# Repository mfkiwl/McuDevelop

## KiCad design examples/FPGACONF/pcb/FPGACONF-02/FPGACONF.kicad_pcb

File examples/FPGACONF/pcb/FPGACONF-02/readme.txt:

### 201911030:
1. FPGACONF-01 + rework
2. the board was not made

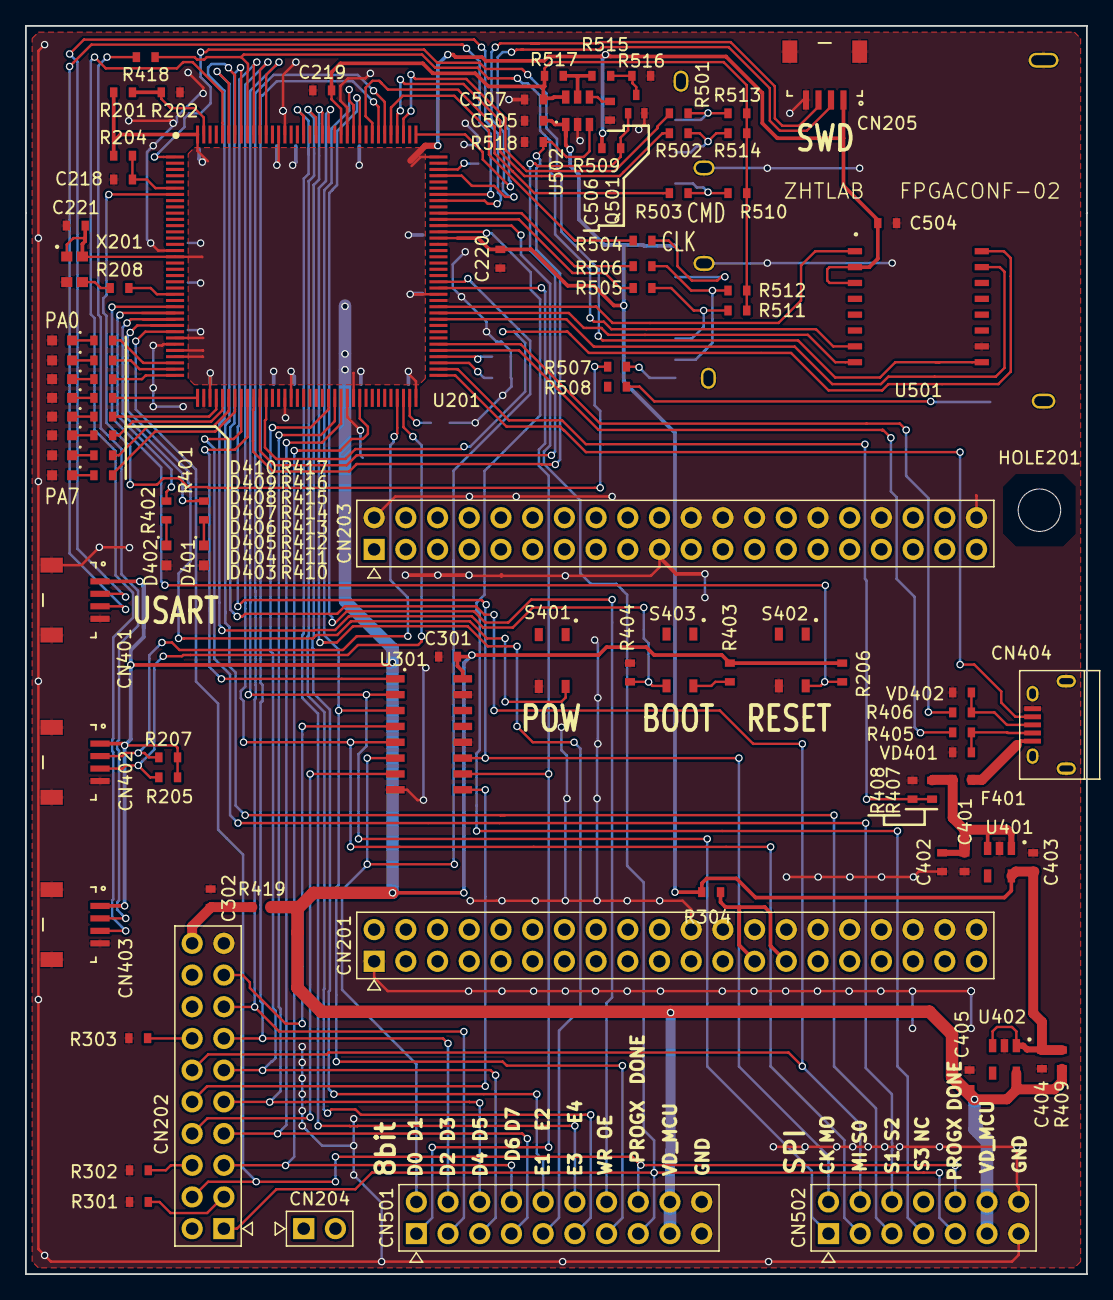
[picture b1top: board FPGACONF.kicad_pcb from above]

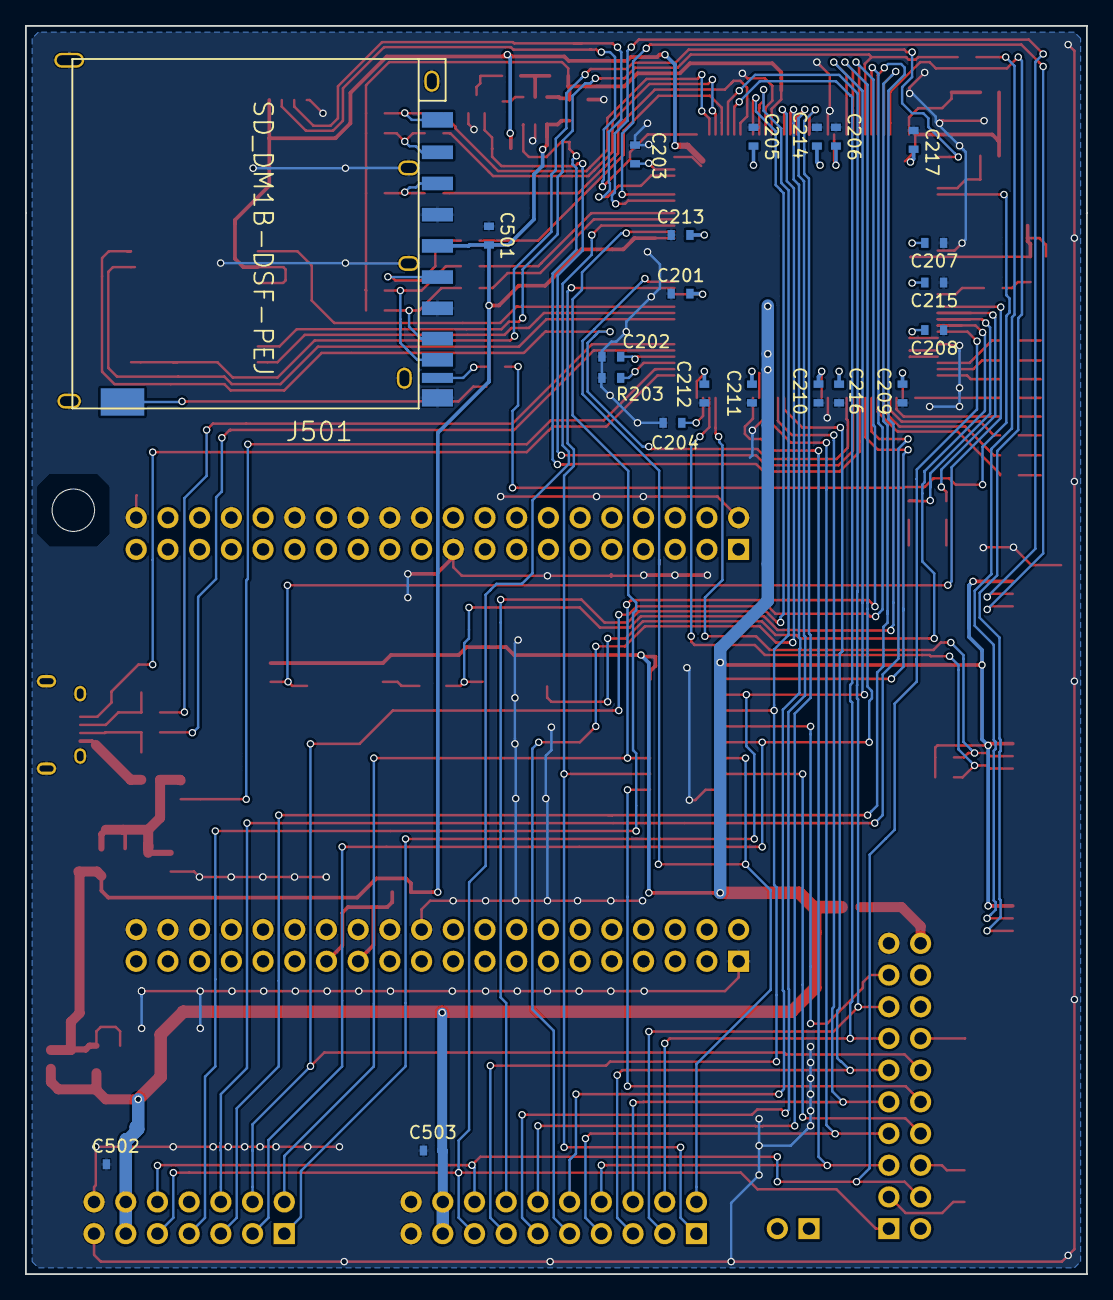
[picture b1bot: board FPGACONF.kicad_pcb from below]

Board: 2 copper layers, 85.0 x 100.0 mm, 121 parts (22 on the bottom side), 110 nets.

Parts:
C201, C205, C206, C207, C208, C209, C210, C211, C212, C217, C218, C219, C220, C221, C301, C504: 0.1u; RCL_1608m
C202, C203, C204, C302, C501, C502, C503, C507: 2.2u; RCL_1608m
C213, C214, C215, C216, C401: 10u; RCL_1608m
C402, C403, C404, C405, C505: 1u; RCL_1608m
C506: 0.01u; RCL_1608m
CN201, CN203: CN_20x2_D1.0mm_P2.54mm_TH
CN202, CN501: CN_10x2_D1.0mm_P2.54mm_TH
CN204: CN_02x1_D1.0mm_P2.54mm_TH; CN_01x2_D1.0mm_P2.54mm_TH
CN205, CN401, CN402, CN403: JST_SM04B-SRSS-TB; JST_SH_SM04B-SRSS-TB_04x1.00mm_Angled
CN404: ZX62D-B-5PA8(30); USB-uB_ZX62D-B-5PA8-30
CN502: CN_07x2_D1.0mm_P2.54mm_TH
D401, D403, D404, D405, D406, D407, D408, D409, D410: SML-E12V8TT86; LED_1608M_Rohm
D402: SML-E13BC8TT86; LED_1608M_Rohm
F401: MFU0603FF03150P500; RCL_1608m
HOLE201: HOLE_01x1_D3.4mm_P0.00mm_NTH; Hole_01x1_D3.4mm_P0.00mm_NTH
J501: SD_DM1B-DSF-PEJ
Q501: RU1C001UN; SC-85_2.0x2.0mm
R201, R205, R206, R207, R401, R402, R403, R410, R411, R412, R413, R414, R415, R416, R417, R510, R511, R512, R513, R514: 4.7k; RCL_1608m
R202, R404, R407, R509, R518: 100k; RCL_1608m
R203: 3.0k; RCL_1608m
R204, R208, R301, R302, R303, R304, R409, R419: 0; RCL_1608m
R405, R406, R418, R501, R502, R503, R504, R505, R506, R507, R508: 22; RCL_1608m
R408: 150k; RCL_1608m
R515: 7.5k; RCL_1608m
R516: 20k; RCL_1608m
R517: 13k; RCL_1608m
S401, S402, S403: SKRPABE010; Alps_SKRPABE010
U201: STM32F730Z8T; TQFP-144_20x20mm_Pitch0.5mm
U301: SN74CBTLV3257D; SOIC-16_3.9x10.0mm_Pitch1.27mm
U401: LP5907MFX-3.3/NOPB; SOT-23-5_2.7x2.9mm_Pitch0.95mm
U402: LP5907MFX-1.8/NOPB; SOT-23-5_2.7x2.9mm_Pitch0.95mm
U501: MT25QL01GBBB8ESF-0SIT; SOIC-16_10.3x10.3mm_Pitch1.27mm
U502: TPS73001DBVR; SOT-23-6_2.7x2.9mm_Pitch0.95mm
VD401, VD402: AVRL161A3R3FTA; RCL_1608m
X201: ASVTX-12-A-40.000MHZ-H10-T; SMD004_abracon_2.5x2.0mm

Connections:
FPGA_CCLK_SCK: CN202.17, U301.4
FPGA_D0_MOSI: CN202.10, U301.9
FPGA_D1_MISO: CN202.8, U301.7
MCU_BOOT: R404.2, S403.4, U201.138
MCU_PA0:LED0: R417.2, U201.34
MCU_PA1:LED1: R416.2, U201.35
MCU_PA2:LED2: R415.2, U201.36
MCU_PA3:LED3: R414.2, U201.37
MCU_PA4:LED4: R413.2, U201.40
MCU_PA5:LED5: R412.2, U201.41
MCU_PA6:LED6: R411.2, U201.42
MCU_PA7:LED7: R410.2, U201.43
MCU_PA9:UART_TXD: CN401.2, U201.101
MCU_PA10:UART_RXD: CN401.3, U201.102
MCU_PA13:SWDIO: CN205.3, U201.105
MCU_PA14:SWCLK: CN205.2, U201.109
MCU_PB0:SDMMC1_PWREN: R518.2, U201.46, U502.3
MCU_PB1:SDMMC1_VSEL33: Q501.1, R509.1, U201.47
MCU_PB2:QSPI_CLK: U201.48, U501.16
MCU_PB3:SPI1_SCK: CN502.1, U201.133, U301.2
MCU_PB4:SPI1_MISO: CN502.3, U201.134, U301.5
MCU_PB5:SPI1_MOSI: CN502.2, U201.135, U301.11
MCU_PB6:I2CS_SCL_QSPI_CSX: R418.2, U201.136, U501.7
MCU_PB7:SPI1_CS0X: CN202.12, CN502.4, U201.137
MCU_PB8:SPI1_CS1X: CN502.5, U201.139
MCU_PB9:I2CS_SDA: CN403.3, U201.140
MCU_PB10:I2CM_SCL: CN402.2, R207.1, U201.69
MCU_PB11:I2CM_SDA: CN402.3, R205.1, U201.70
MCU_PB12:USB_ID: CN404.4, U201.73
MCU_PB13:USB_VBUS_EN: R407.2, R408.2, U201.74
MCU_PB14:USB_DN: R405.2, U201.77
MCU_PB15:USB_DP: R406.2, U201.78
MCU_PC0:LED_BLUE: R402.2, U201.26
MCU_PC1:LED_RED: R401.2, U201.27
MCU_PC2:POWER_SW_X: S401.2, U201.28
MCU_PC3:FPGA_DONE: CN202.4, CN501.16, CN502.10, U201.29
MCU_PC4:SPI1_CS2X: CN502.6, U201.44
MCU_PC5:CONF_SEL: U201.45, U301.1
MCU_PC6:SPI1_CS3X: CN502.7, U201.96
MCU_PC7:FPGA_PROGX: CN202.1, CN501.15, CN502.9, U201.97
MCU_PC8:SDMMC1_D0: R505.1, U201.98
MCU_PC9:SDMMC1_D1: R506.1, U201.99
MCU_PC10:SDMMC1_D2: R501.1, U201.111
MCU_PC11:SDMMC1_D3: R502.1, U201.112
MCU_PC12:SDMMC1_CLK: R504.1, U201.113
MCU_PC13:SDMMC1_CDET_X: R507.1, U201.7
MCU_PD0:FMC_D2: CN202.15, CN501.3, U201.114
MCU_PD1:FMC_D3: CN202.13, CN501.4, U201.115
MCU_PD2:SDMMC1_CMD: R503.1, U201.116
MCU_PD4:FMC_NOE: CN501.14, U201.118
MCU_PD5:FMC_NWE: CN501.13, U201.119, U301.3
MCU_PD7:FMC_NE1: CN501.9, U201.123
MCU_PD11:QSPI_D0: U201.82, U501.15
MCU_PD12:QSPI_D1: U201.83, U501.8
MCU_PD13:QSPI_D3: U201.84, U501.1
MCU_PD14:FMC_D0: CN501.1, U201.87, U301.10
MCU_PD15:FMC_D1: CN501.2, U201.88, U301.6
MCU_PE2:QSPI_D2: U201.1, U501.9
MCU_PE7:FMC_D4: CN202.11, CN501.5, U201.58
MCU_PE8:FMC_D5: CN202.9, CN501.6, U201.59
MCU_PE9:FMC_D6: CN202.7, CN501.7, U201.60
MCU_PE10:FMC_D7: CN202.5, CN501.8, U201.63
MCU_PG9:FMC_NE2: CN501.10, U201.124
MCU_PG10:FMC_NE3: CN501.11, U201.125
MCU_PG12:FMC_NE4: CN501.12, U201.127
MCU_RESET_SW_X: R206.1, S402.2, U201.25
unnamed: C202.2, U201.76
unnamed: C203.2, U201.106
unnamed: C204.2, U201.71
unnamed: C218.2, R204.2, U201.6
unnamed: C506.2, U502.4
unnamed: CN201.25, CN201.27, R304.1
unnamed: CN202.3, R301.2
unnamed: CN202.6, R302.1
unnamed: CN202.14, R303.1
unnamed: CN403.2, R418.1
unnamed: CN404.1, F401.1
unnamed: CN404.2, R405.1, VD401.1
unnamed: CN404.3, R406.1, VD402.1
unnamed: D401.1, R401.1
unnamed: D402.1, R402.1
unnamed: D403.1, R410.1
unnamed: D404.1, R411.1
unnamed: D405.1, R412.1
unnamed: D406.1, R413.1
unnamed: D407.1, R414.1
unnamed: D408.1, R415.1
unnamed: D409.1, R416.1
unnamed: D410.1, R417.1
unnamed: J501.1, R502.2, R514.1
unnamed: J501.2, R503.2, R510.1
unnamed: J501.5, R504.2
unnamed: J501.7, R505.2, R511.1
unnamed: J501.8, R506.2, R512.1
unnamed: J501.9, R501.2, R513.1
unnamed: J501.10, R507.2
unnamed: J501.12, R508.2
unnamed: Q501.3, R515.1, R516.2
unnamed: R201.1, R202.2, U201.143
unnamed: R203.2, U201.75
unnamed: R208.1, X201.3
unnamed: R208.2, U201.23
unnamed: R403.1, S403.2
unnamed: R515.2, R517.1, U502.5
VD3P30: C220.2, C403.2, C404.2, C501.2, C505.2, J501.4, R304.2, R409.1, U201.95, U401.5, U402.1, U402.3, U502.1
VD5P00: C401.1, C402.2, F401.2, R407.1, U401.1, U401.3
VD_MCU: C201.2, C205.2, C206.2, C207.2, C208.2, C209.2, C210.2, C211.2, C212.2, C213.2, C214.2, C215.2, C216.2, C217.2, C221.2, C301.2, C405.2, C502.2, C503.2, C504.2, CN205.1, CN401.1, CN402.1, CN403.1, CN501.17, CN501.18, CN502.11, CN502.12, R201.2, R204.1, R205.2, R206.2, R207.2, R403.2, R409.2, R419.2, R509.2, U201.17, U201.30, U201.32, U201.33, U201.39, U201.52, U201.62, U201.72, U201.86, U201.108, U201.131, U201.144, U301.16, U402.5, U501.2, U501.3, X201.1, X201.4
VD_SDIO: C219.2, C507.2, R510.2, R511.2, R512.2, R513.2, R514.2, R517.2, U201.121, U502.6
VD_VCCIO8: C302.2, CN202.20, R419.1
~: C201.1, C202.1, C203.1, C204.1, C205.1, C206.1, C207.1, C208.1, C209.1, C210.1, C211.1, C212.1, C213.1, C214.1, C215.1, C216.1, C217.1, C218.1, C219.1, C220.1, C221.1, C301.1, C302.1, C401.2, C402.1, C403.1, C404.1, C405.1, C501.1, C502.1, C503.1, C504.1, C505.1, C506.1, C507.1, CN201.1, CN201.22, CN201.24, CN201.26, CN201.28, CN201.30, CN201.32, CN201.34, CN201.36, CN201.38, CN201.40, CN202.19, CN203.2, CN203.19, CN203.22, CN203.24, CN203.26, CN203.30, CN203.34, CN203.40, CN205.4, CN205.5, CN205.6, CN401.4, CN401.5, CN401.6, CN402.4, CN402.5, CN402.6, CN403.4, CN403.5, CN403.6, CN404.5, CN404.6, CN404.7, CN404.8, CN404.9, CN501.19, CN501.20, CN502.13, CN502.14, D401.2, D402.2, D403.2, D404.2, D405.2, D406.2, D407.2, D408.2, D409.2, D410.2, J501.3, J501.6, J501.11, J501.13, J501.14, J501.15, J501.16, J501.17, J501.18, Q501.2, R202.1, R203.1, R301.1, R302.2, R303.2, R404.1, R408.1, R516.1, R518.1, S401.4, S402.4, U201.16, U201.31, U201.38, U201.51, U201.61, U201.85, U201.94, U201.107, U201.120, U201.130, U301.8, U301.12, U301.15, U401.2, U402.2, U501.10, U502.2, VD401.2, VD402.2, X201.2

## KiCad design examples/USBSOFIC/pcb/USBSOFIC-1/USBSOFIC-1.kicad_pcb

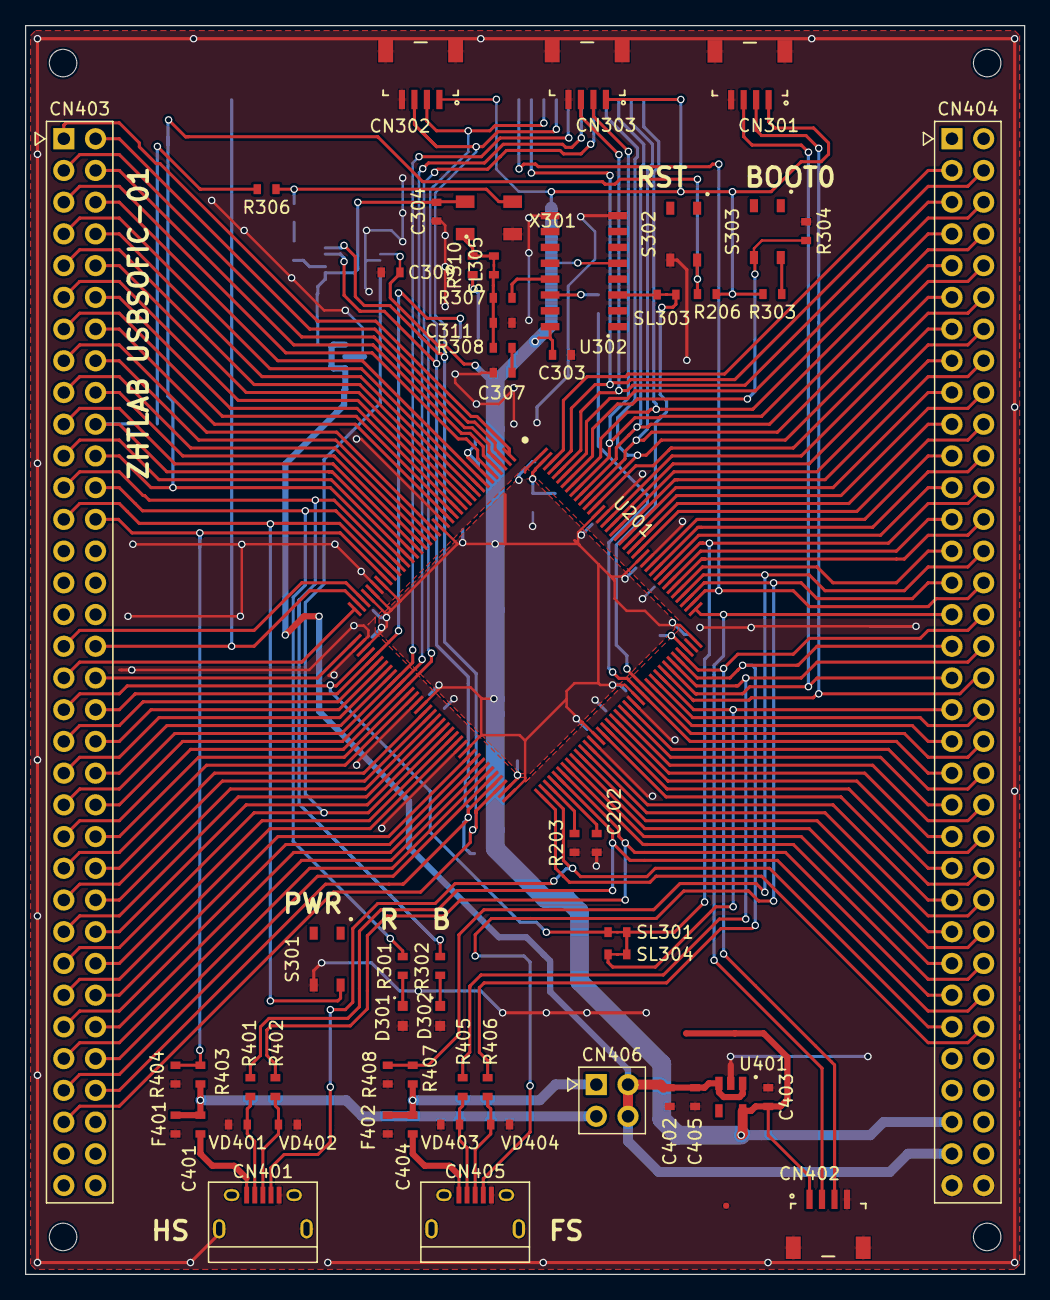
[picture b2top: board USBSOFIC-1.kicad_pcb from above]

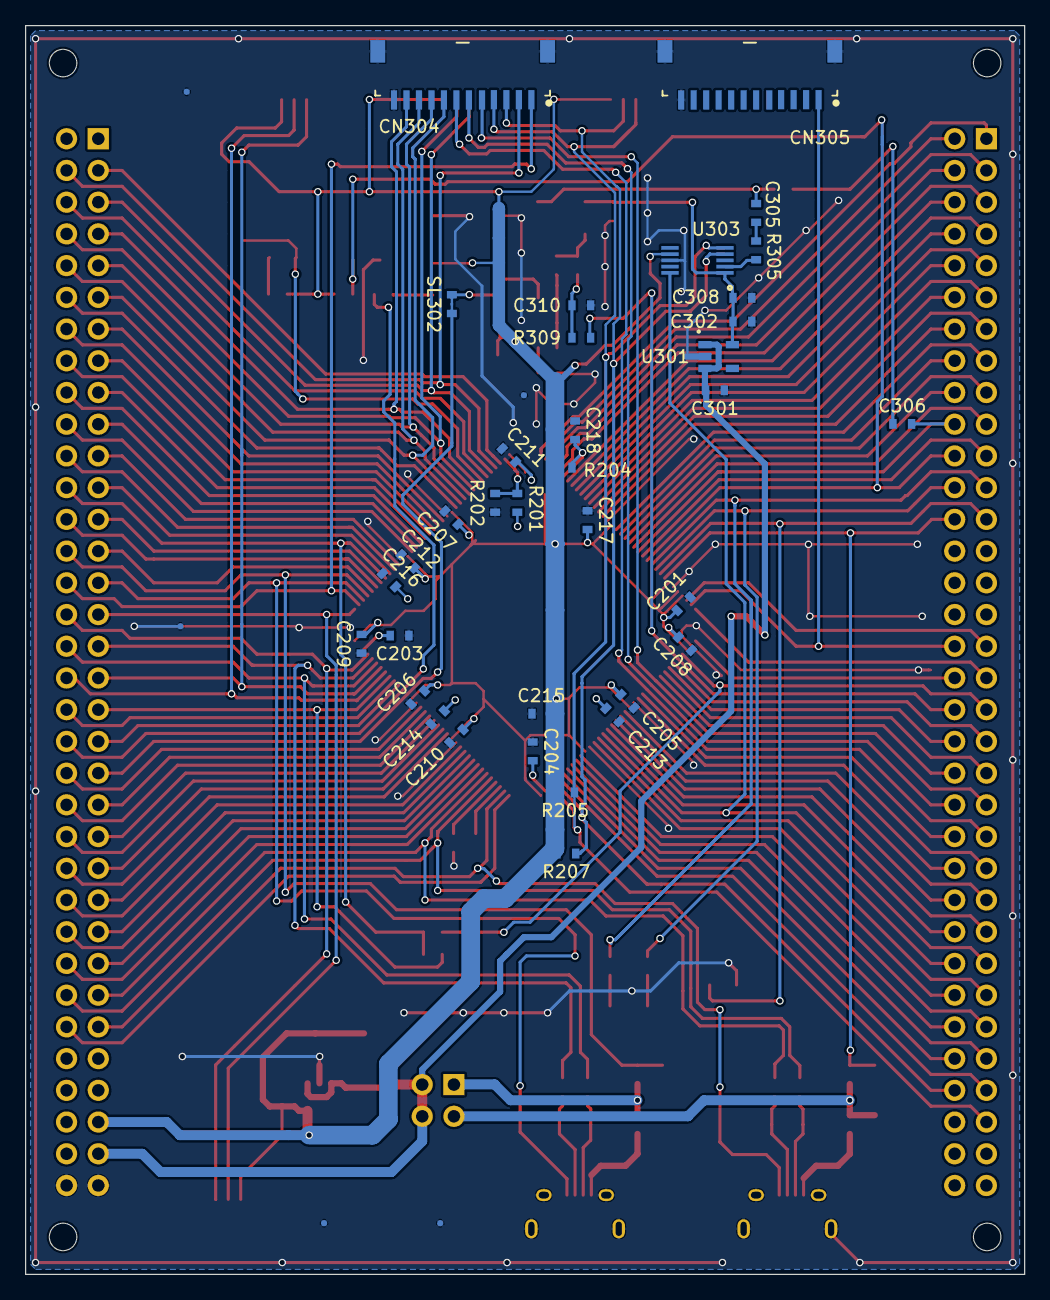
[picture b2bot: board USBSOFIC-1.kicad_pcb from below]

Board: 2 copper layers, 80.0 x 100.0 mm, 108 parts (44 on the bottom side), 146 nets.

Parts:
C201, C205, C206, C207, C208, C209, C210, C211, C212, C217, C218, C303, C304, C305, C306, C308, C309, C310: 0.1u; RCL_1608m
C202, C203, C204: 2.2u; RCL_1608m
C213, C214, C215, C216, C401, C404, C405: 10u; RCL_1608m
C301, C302, C307, C311, C402, C403: 1u; RCL_1608m
CN301, CN302, CN303, CN402: JST_SM04B-SRSS-TB; JST_SH_SM04B-SRSS-TB_04x1.00mm_Angled
CN304, CN305: JST_SM12B-SHSS-TB; JST_SH_SM12B-SRSS-TB_04x1.00mm_Angled
CN401, CN405: ZX62D-B-5PA8(30); USB-uB_ZX62D-B-5PA8-30
CN403, CN404: CN_34x2_D1.0mm_P2.54mm_TH
CN406: CN_02x2_D1.0mm_P2.54mm_TH
D301: SML-E12V8TT86; LED_1608M_Rohm
D302: SML-E13BC8TT86; LED_1608M_Rohm
F401, F402: MFU0603FF03150P500; RCL_1608m
HOLE401, HOLE402, HOLE403, HOLE404: HOLE-2.2mm-NTH; Hole_01x1_D2.2mm_P0.00mm_NTH
R201, R205, R206, R207, R301, R302, R303: 4.7k; RCL_1608m
R202, R304, R403, R407: 100k; RCL_1608m
R203: 3.0k; RCL_1608m
R204, R308, R310: 0; RCL_1608m
R305, R306, R309: 10; RCL_1608m
R307: 16k; RCL_1608m
R401, R402, R405, R406: 22; RCL_1608m
R404, R408: 150k; RCL_1608m
S301, S302, S303: SKRPABE010; Alps_SKRPABE010
SL301, SL302, SL303, SL304, SL305: SL-1608M; SL_1608m
TP401, TP402, TP403, TP404, TP405, TP406, TP407, TP408, TP409, TP410, TP411, TP412: TP-C05N; TP_C0.5mm_nonsolder
U201: STM32F730Z8T; TQFP-144_20x20mm_Pitch0.5mm
U301: LP5907MFX-3.0/NOPB; SOT-23-5_2.7x2.9mm_Pitch0.95mm
U302: CD74HC4046AM96; SOIC-16_3.9x10.0mm_Pitch1.27mm
U303: SI5351A-B-GT; MSOP-10_3.0x3.0mm_Pitch0.5mm
U401: LP5907MFX-3.3/NOPB; SOT-23-5_2.7x2.9mm_Pitch0.95mm
VD401, VD402, VD403, VD404: AVRL161A3R3FTA; RCL_1608m
X301: ASVTX-09-26000; SMD004_abracon_5.0x3.2mm

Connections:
CLK26M000_VC: R310.2, SL305.2, X301.1
GND: C201.1, C202.1, C203.1, C204.1, C205.1, C206.1, C207.1, C208.1, C209.1, C210.1, C211.1, C212.1, C213.1, C214.1, C215.1, C216.1, C217.1, C218.1, C301.1, C302.1, C303.1, C304.1, C307.1, C308.1, C309.1, C310.1, C311.1, C401.2, C402.1, C403.1, C404.2, C405.2, CN301.4, CN301.5, CN301.6, CN302.4, CN302.5, CN302.6, CN303.4, CN303.5, CN303.6, CN304.12, CN304.13, CN304.14, CN305.12, CN305.13, CN305.14, CN401.5, CN401.6, CN401.7, CN401.8, CN401.9, CN402.4, CN402.5, CN402.6, CN404.67, CN404.68, CN405.5, CN405.6, CN405.7, CN405.8, CN405.9, D301.2, D302.2, R202.1, R203.1, R304.1, R404.1, R408.1, S301.4, S302.4, TP402.1, TP404.1, TP406.1, TP408.1, TP410.1, TP412.1, U201.16, U201.31, U201.38, U201.51, U201.61, U201.85, U201.94, U201.107, U201.120, U201.130, U301.2, U302.8, U302.9, U303.8, U401.2, VD401.2, VD402.2, VD403.2, VD404.2, X301.2
MCU_BOOT: R304.2, S303.4, U201.138
MCU_PA0: CN403.33, U201.34
MCU_PA1:SYNC_FRAME: CN305.1, CN403.34, U201.35
MCU_PA2: CN403.35, U201.36
MCU_PA3: CN403.36, U201.37
MCU_PA4: CN403.37, SL301.1, U201.40
MCU_PA5:DAC_OUT2: CN403.38, R309.1, U201.41
MCU_PA6: CN403.39, U201.42
MCU_PA7: CN403.40, U201.43
MCU_PA8: CN404.37, SL304.1, U201.100
MCU_PA9:UART_TXD: CN301.2, CN404.36, U201.101
MCU_PA10:UART_RXD: CN301.3, CN404.35, U201.102
MCU_PA11:USB_DN: CN404.34, R405.2, U201.103
MCU_PA12:USB_DP: CN404.33, R406.2, U201.104
MCU_PA13:SWDIO: CN402.3, CN404.32, U201.105
MCU_PA14:SWCLK: CN402.2, CN404.31, U201.109
MCU_PA15:CLK: CN304.1, CN404.30, U201.110
MCU_PB0:SEL0: CN304.5, CN403.43, U201.46
MCU_PB1:SEL1: CN304.6, CN403.44, U201.47
MCU_PB2:SEL2: CN304.7, CN403.45, U201.48
MCU_PB3:SPI1_SCK: CN304.8, CN404.11, U201.133
MCU_PB4:SPI1_MISO: CN304.10, CN404.10, U201.134
MCU_PB5:SPI1_MOSI: CN304.9, CN404.9, U201.135
MCU_PB6:I2CS_SCL: CN303.2, CN404.8, U201.136
MCU_PB7:SPI1_CSX: CN304.11, CN404.7, U201.137
MCU_PB8: CN404.6, U201.139
MCU_PB9:I2CS_SDA: CN303.3, CN404.5, U201.140
MCU_PB10:I2CM_SCL: CN302.2, CN304.3, CN403.62, R207.1, U201.69, U303.4
MCU_PB11:I2CM_SDA: CN302.3, CN304.4, CN403.63, R205.1, U201.70, U303.5
MCU_PB12: CN404.58, U201.73
MCU_PB13:USB_ID: CN401.4, CN404.57, U201.74
MCU_PB14:USB_DN: CN404.56, R401.2, U201.77
MCU_PB15:USB_DP: CN404.55, R402.2, U201.78
MCU_PC0:LED_BLUE: CN403.23, R302.2, U201.26
MCU_PC1:LED_RED: CN403.24, R301.2, U201.27
MCU_PC2:POWER_SW_X: CN403.25, S301.2, U201.28
MCU_PC3:USB_VBUS_EN: CN403.26, R403.2, R404.2, U201.29
MCU_PC4: CN403.41, U201.44
MCU_PC5: CN403.42, U201.45
MCU_PC6: CN404.41, SL302.1, U201.96
MCU_PC7: CN404.40, SL303.1, U201.97
MCU_PC8: CN404.39, U201.98
MCU_PC9: CN404.38, U201.99
MCU_PC10:USB_ID: CN404.29, CN405.4, U201.111
MCU_PC11:USB_VBUS_EN: CN404.28, R407.2, R408.2, U201.112
MCU_PC12: CN404.27, U201.113
MCU_PC13: CN403.6, U201.7
MCU_PC14: CN403.7, U201.8
MCU_PC15: CN403.8, U201.9
MCU_PD0: CN404.26, U201.114
MCU_PD1: CN404.25, U201.115
MCU_PD2: CN404.24, SL301.2, SL304.2, U201.116
MCU_PD3: CN404.23, U201.117
MCU_PD4: CN404.22, U201.118
MCU_PD5: CN404.21, U201.119
MCU_PD6: CN404.20, U201.122
MCU_PD7: CN404.19, U201.123
MCU_PD8: CN404.54, U201.79
MCU_PD9: CN404.53, U201.80
MCU_PD10: CN404.52, U201.81
MCU_PD11: CN404.51, U201.82
MCU_PD12: CN404.50, U201.83
MCU_PD13: CN404.49, U201.84
MCU_PD14: CN404.48, U201.87
MCU_PD15: CN404.47, U201.88
MCU_PE0:SYNC: CN304.2, CN404.4, U201.141
MCU_PE1: CN404.3, U201.142
MCU_PE2: CN403.1, U201.1
MCU_PE3: CN403.2, U201.2
MCU_PE4: CN403.3, U201.3
MCU_PE5: CN403.4, U201.4
MCU_PE6: CN403.5, U201.5
MCU_PE7:CLK24M576: CN403.53, U201.58, U303.10
MCU_PE8: CN403.54, U201.59
MCU_PE9: CN403.55, U201.60
MCU_PE10: CN403.56, U201.63
MCU_PE11: CN403.57, U201.64
MCU_PE12: CN403.58, U201.65
MCU_PE13: CN403.59, U201.66
MCU_PE14: CN403.60, U201.67
MCU_PE15: CN403.61, U201.68
MCU_PF0: CN403.9, U201.10
MCU_PF1: CN403.10, U201.11
MCU_PF2: CN403.11, U201.12
MCU_PF3: CN403.12, U201.13
MCU_PF4: CN403.13, U201.14
MCU_PF5: CN403.14, U201.15
MCU_PF6: CN403.15, U201.18
MCU_PF7: CN403.16, U201.19
MCU_PF8: CN403.17, U201.20
MCU_PF9: CN403.18, U201.21
MCU_PF10: CN403.19, U201.22
MCU_PF11: CN403.46, U201.49
MCU_PF12: CN403.47, U201.50
MCU_PF13: CN403.48, U201.53
MCU_PF14: CN403.49, U201.54
MCU_PF15: CN403.50, U201.55
MCU_PG0: CN403.51, U201.56
MCU_PG1: CN403.52, U201.57
MCU_PG2: CN404.46, U201.89
MCU_PG3: CN404.45, U201.90
MCU_PG4: CN404.44, U201.91
MCU_PG5: CN404.43, U201.92
MCU_PG8: CN404.42, U201.93
MCU_PG9: CN404.18, U201.124
MCU_PG10: CN404.17, U201.125
MCU_PG11: CN404.16, U201.126
MCU_PG12: CN404.15, U201.127
MCU_PG13: CN404.14, U201.128
MCU_PG14: CN404.13, U201.129
MCU_PG15: CN404.12, U201.132
MCU_PH0:CLK26M000_MCU: C306.2, CN403.20, U201.23
MCU_PH1: CN403.21, U201.24
MCU_RESET_SW_X: CN403.22, R206.1, S302.2, U201.25
unnamed: C202.2, U201.76
unnamed: C203.2, U201.106
unnamed: C204.2, U201.71
unnamed: C218.2, R204.2, U201.6
unnamed: C302.2, C304.2, C308.2, U301.5, U303.1, X301.4
unnamed: C305.1, R305.2
unnamed: C305.2, U303.2
unnamed: C306.1, R306.2
unnamed: C307.2, R308.1
unnamed: C310.2, R309.2, R310.1
unnamed: C311.2, R307.2, R308.2, SL305.1
unnamed: CN401.1, F401.1
unnamed: CN401.2, R401.1, VD401.1
unnamed: CN401.3, R402.1, VD402.1
unnamed: CN405.1, F402.1
unnamed: CN405.2, R405.1, VD403.1
unnamed: CN405.3, R406.1, VD404.1
unnamed: D301.1, R301.1
unnamed: D302.1, R302.1
unnamed: R201.1, R202.2, U201.143
unnamed: R203.2, U201.75
unnamed: R303.1, S303.2
unnamed: R305.1, R306.1, X301.3
unnamed: R307.1, U302.13
PD_IN1: SL303.2, U302.3
SOF8DIV: SL302.2, U302.14
VD5P00: C301.2, C402.2, C405.1, CN404.65, CN406.2, CN406.4, U301.1, U301.3, U401.1, U401.3
VD5P00_VBUS_FS: C404.1, CN406.1, F402.2, R407.1
VD5P00_VBUS_HS: C401.1, CN406.3, F401.2, R403.1
VD_MCU: C201.2, C205.2, C206.2, C207.2, C208.2, C209.2, C210.2, C211.2, C212.2, C213.2, C214.2, C215.2, C216.2, C217.2, C303.2, C309.2, C403.2, CN301.1, CN302.1, CN303.1, CN402.1, CN404.63, R201.2, R204.1, R205.2, R206.2, R207.2, R303.2, TP401.1, TP403.1, TP405.1, TP407.1, TP409.1, TP411.1, U201.17, U201.30, U201.32, U201.33, U201.39, U201.52, U201.62, U201.72, U201.86, U201.95, U201.108, U201.121, U201.131, U201.144, U302.5, U302.16, U303.7, U401.5

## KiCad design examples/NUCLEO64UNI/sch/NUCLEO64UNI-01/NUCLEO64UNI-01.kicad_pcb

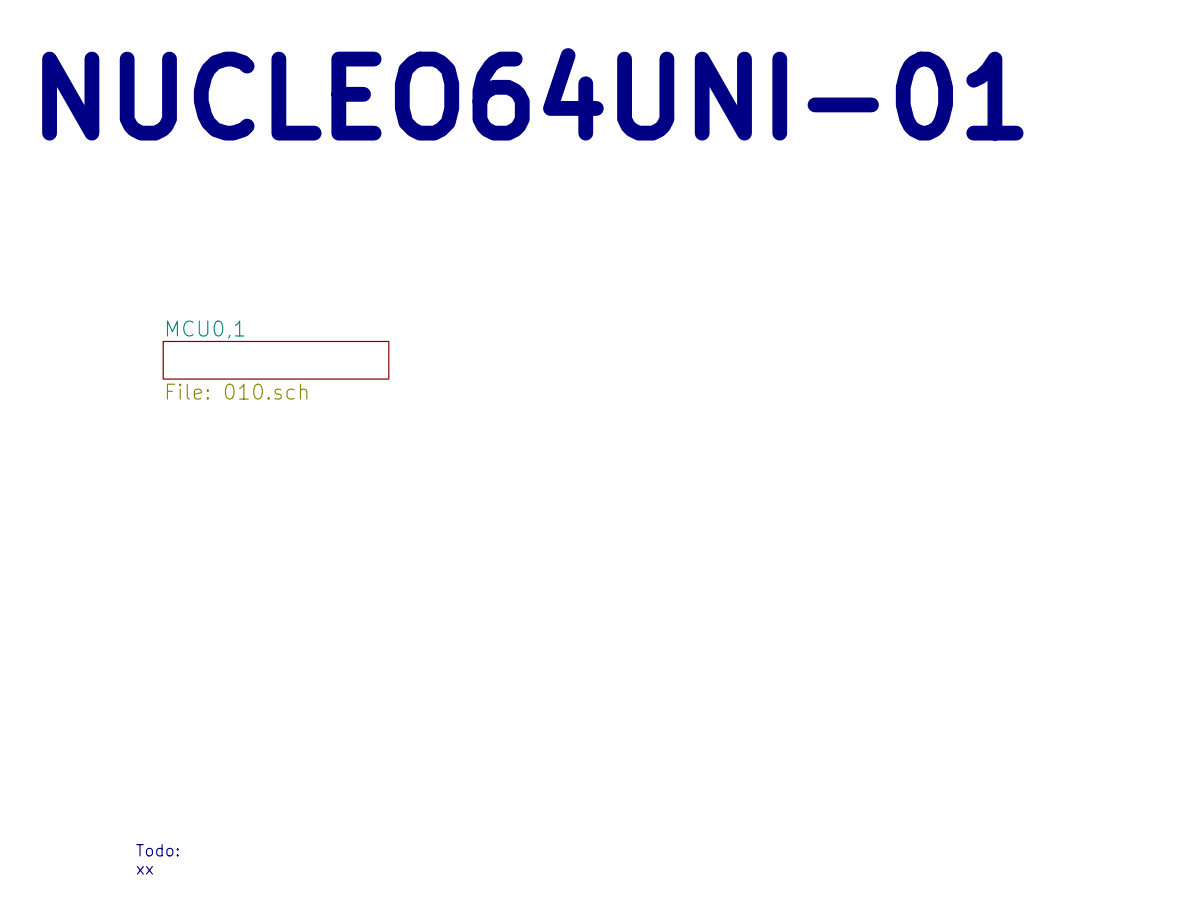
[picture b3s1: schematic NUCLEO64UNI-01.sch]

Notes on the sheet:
NUCLEO64UNI-01
Todo: xx

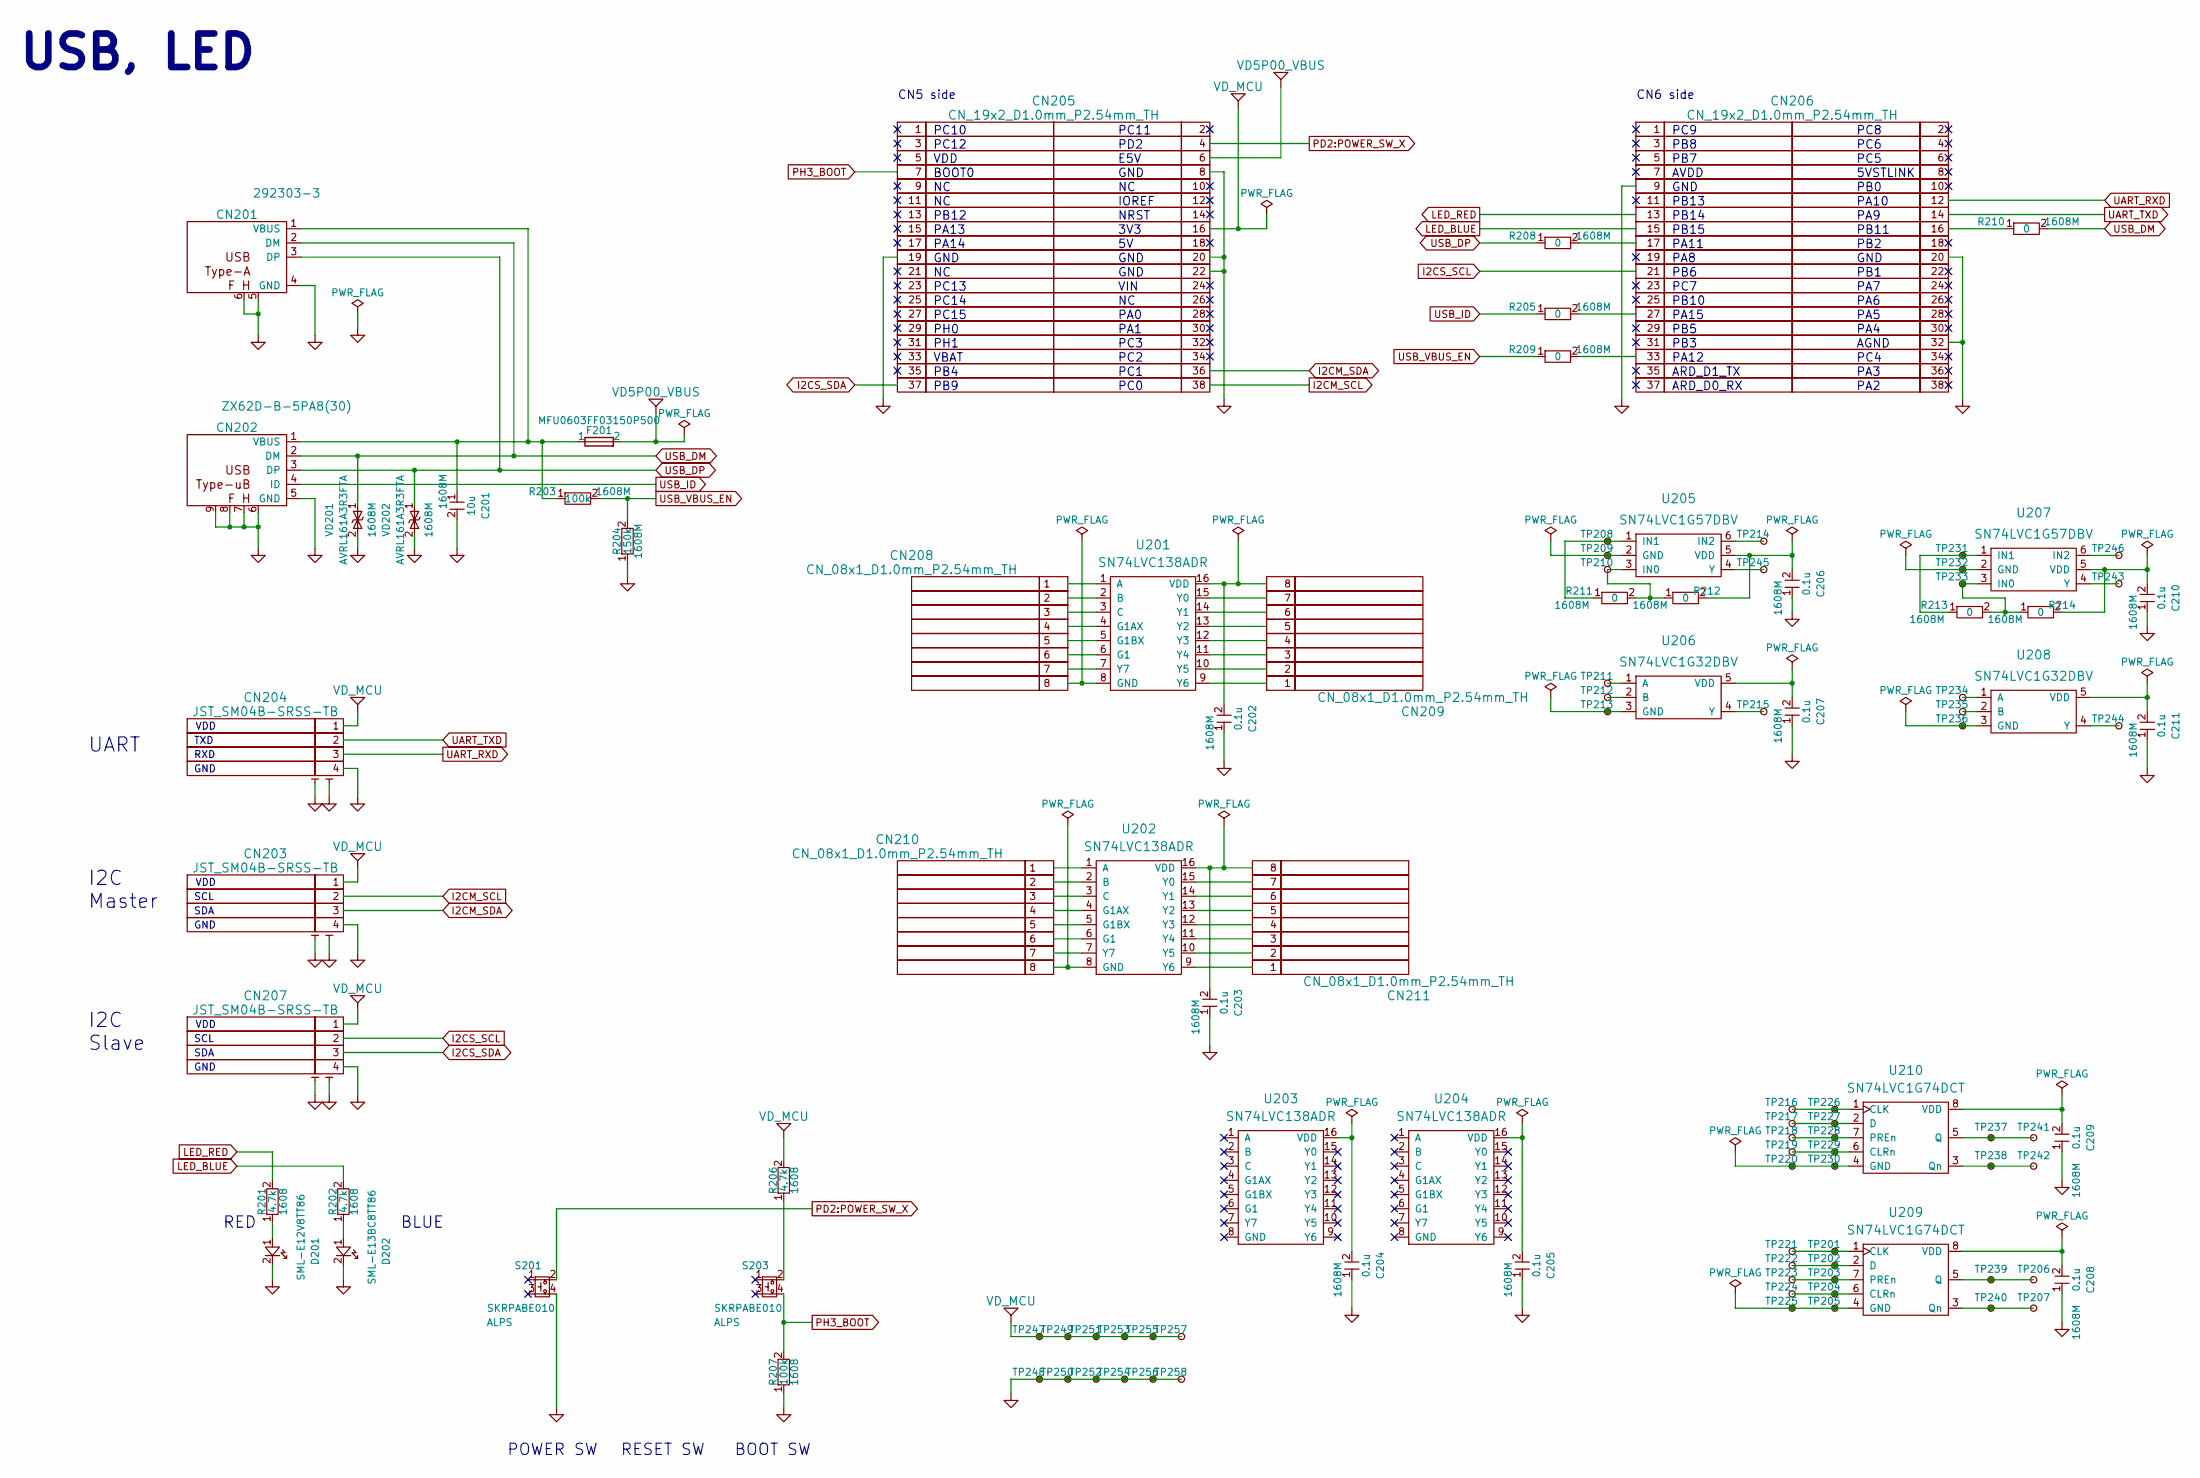
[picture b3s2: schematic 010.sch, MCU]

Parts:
C201: 10u; RCL_1608m
C202, C203, C204, C205, C206, C207, C208, C209, C210, C211: 0.1u; RCL_1608m
CN201: 292303-3; USB_A
CN202: ZX62D-B-5PA8(30); USB_Micro-B
CN203, CN204, CN207: JST_SM04B-SRSS-TB; JST_SH_SM04B-SRSS-TB_04x1.00mm_Angled
CN205, CN206: CN_19x2_D1.0mm_P2.54mm_TH
CN208, CN209, CN210, CN211: CN_08x1_D1.0mm_P2.54mm_TH
D201: SML-E12V8TT86; LED_1608M_Rohm
D202: SML-E13BC8TT86; LED_1608M_Rohm
F201: MFU0603FF03150P500; RCL_1608m
R201, R202, R206: 4.7k; RCL_1608m; Tolerance 5%
R203, R207: 100k; RCL_1608m; Tolerance 5%
R204: 150k; RCL_1608m; Tolerance 5%
R205, R208, R209, R210, R211, R212, R213, R214: 0; RCL_1608m; Tolerance 5%
S201, S203: SKRPABE010; Alps_SKRPABE010
TP201, TP202, TP203, TP204, TP205, TP206, TP207, TP208, TP209, TP210, TP211, TP212, TP213, TP214, TP215, TP216, TP217, TP218, TP219, TP220, TP221, TP222, TP223, TP224, TP225, TP226, TP227, TP228, TP229, TP230, TP231, TP232, TP233, TP234, TP235, TP236, TP237, TP238, TP239, TP240, TP241, TP242, TP243, TP244, TP245, TP246, TP247, TP248, TP249, TP250, TP251, TP252, TP253, TP254, TP255, TP256, TP257, TP258: TP-C05N; TP_C0.5mm_nonsolder
U201, U202, U203, U204: SN74LVC138ADR; SOIC-16_3.9x10.0mm_Pitch1.27mm
U205, U207: SN74LVC1G57DBV; SOT-23-6_2.7x2.9mm_Pitch0.95mm
U206, U208: SN74LVC1G32DBV; SOT-23-5_2.7x2.9mm_Pitch0.95mm
U209, U210: SN74LVC1G74DCT; MSOP-8_2.8x2.9mm_Pitch0.65mm
VD201, VD202: AVRL161A3R3FTA; RCL_1608m

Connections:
GND: C201.2, C202.1, C203.1, C204.1, C205.1, C206.1, C207.1, C208.1, C209.1, C210.1, C211.1, CN201.4 (GND), CN201.5, CN201.6, CN202.5 (GND), CN202.6, CN202.7, CN202.8, CN202.9, CN203.4, CN203.5, CN203.6, CN204.4, CN204.5, CN204.6, CN205.8, CN205.19, CN205.20, CN205.22, CN206.9, CN206.20, CN206.32, CN207.4, CN207.5, CN207.6, D201.2, D202.2, R204.1, R207.1, S201.4, TP248.1, TP250.1, TP252.1, TP254.1, TP256.1, TP258.1, VD201.2, VD202.2
I2CM_SCL: CN203.2, CN205.38
I2CM_SDA: CN203.3, CN205.36
I2CS_SCL: CN206.21, CN207.2
I2CS_SDA: CN205.37, CN207.3
LED_BLUE: CN206.15, R202.2
LED_RED: CN206.13, R201.2
unnamed: C201.1, CN201.1 (VBUS), CN202.1 (VBUS), F201.1, R203.1
unnamed: C202.2, CN209.8, U201.16 (VDD)
unnamed: C203.2, CN211.8, U202.16 (VDD)
unnamed: C204.2, U203.16 (VDD)
unnamed: C205.2, U204.16 (VDD)
unnamed: C206.2, R212.2, U205.5 (VDD)
unnamed: C207.2, U206.5 (VDD)
unnamed: C208.2, U209.8 (VDD)
unnamed: C209.2, U210.8 (VDD)
unnamed: C210.2, R214.2, U207.5 (VDD)
unnamed: C211.2, U208.5 (VDD)
unnamed: CN206.16, R210.1
unnamed: CN206.17, R208.2
unnamed: CN206.27, R205.2
unnamed: CN206.33, R209.2
unnamed: CN208.1, U201.1 (A)
unnamed: CN208.2, U201.2 (B)
unnamed: CN208.3, U201.3 (C)
unnamed: CN208.4, U201.4 (G1AX)
unnamed: CN208.5, U201.5 (G1BX)
unnamed: CN208.6, U201.6 (G1)
unnamed: CN208.7, U201.7 (Y7)
unnamed: CN208.8, U201.8 (GND)
unnamed: CN209.1, U201.9 (Y6)
unnamed: CN209.2, U201.10 (Y5)
unnamed: CN209.3, U201.11 (Y4)
unnamed: CN209.4, U201.12 (Y3)
unnamed: CN209.5, U201.13 (Y2)
unnamed: CN209.6, U201.14 (Y1)
unnamed: CN209.7, U201.15 (Y0)
unnamed: CN210.1, U202.1 (A)
unnamed: CN210.2, U202.2 (B)
unnamed: CN210.3, U202.3 (C)
unnamed: CN210.4, U202.4 (G1AX)
unnamed: CN210.5, U202.5 (G1BX)
unnamed: CN210.6, U202.6 (G1)
unnamed: CN210.7, U202.7 (Y7)
unnamed: CN210.8, U202.8 (GND)
unnamed: CN211.1, U202.9 (Y6)
unnamed: CN211.2, U202.10 (Y5)
unnamed: CN211.3, U202.11 (Y4)
unnamed: CN211.4, U202.12 (Y3)
unnamed: CN211.5, U202.13 (Y2)
unnamed: CN211.6, U202.14 (Y1)
unnamed: CN211.7, U202.15 (Y0)
unnamed: D201.1, R201.1
unnamed: D202.1, R202.1
unnamed: R206.1, S203.2
unnamed: R211.1, TP208.1, U205.1 (IN1)
unnamed: R211.2, R212.1, TP210.1, U205.3 (IN0)
unnamed: R213.1, TP231.1, U207.1 (IN1)
unnamed: R213.2, R214.1, TP233.1, U207.3 (IN0)
unnamed: TP201.1, TP221.1, U209.1 (CLK)
unnamed: TP202.1, TP222.1, U209.2 (D)
unnamed: TP203.1, TP223.1, U209.7 (PREn)
unnamed: TP204.1, TP224.1, U209.6 (CLRn)
unnamed: TP205.1, TP225.1, U209.4 (GND)
unnamed: TP206.1, TP239.1, U209.5 (Q)
unnamed: TP207.1, TP240.1, U209.3 (Qn)
unnamed: TP209.1, U205.2 (GND)
unnamed: TP211.1, U206.1 (A)
unnamed: TP212.1, U206.2 (B)
unnamed: TP213.1, U206.3 (GND)
unnamed: TP214.1, U205.6 (IN2)
unnamed: TP215.1, U206.4 (Y)
unnamed: TP216.1, TP226.1, U210.1 (CLK)
unnamed: TP217.1, TP227.1, U210.2 (D)
unnamed: TP218.1, TP228.1, U210.7 (PREn)
unnamed: TP219.1, TP229.1, U210.6 (CLRn)
unnamed: TP220.1, TP230.1, U210.4 (GND)
unnamed: TP232.1, U207.2 (GND)
unnamed: TP234.1, U208.1 (A)
unnamed: TP235.1, U208.2 (B)
unnamed: TP236.1, U208.3 (GND)
unnamed: TP237.1, TP241.1, U210.5 (Q)
unnamed: TP238.1, TP242.1, U210.3 (Qn)
unnamed: TP243.1, U207.4 (Y)
unnamed: TP244.1, U208.4 (Y)
unnamed: TP245.1, U205.4 (Y)
unnamed: TP246.1, U207.6 (IN2)
PD2:POWER_SW_X: CN205.4, S201.2
PH3_BOOT: CN205.7, R207.2, S203.4
UART_RXD: CN204.3, CN206.12
UART_TXD: CN204.2, CN206.14
USB_DM: CN201.2 (DM), CN202.2 (DM), R210.2, VD201.1
USB_DP: CN201.3 (DP), CN202.3 (DP), R208.1, VD202.1
USB_ID: CN202.4 (ID), R205.1
USB_VBUS_EN: R203.2, R204.2, R209.1
VD5P00: CN205.6, F201.2
VD_MCU: CN203.1, CN204.1, CN205.16, CN207.1, R206.2, TP247.1, TP249.1, TP251.1, TP253.1, TP255.1, TP257.1

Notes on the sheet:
USB, LED
RESET SW
BOOT SW
POWER SW
RED
BLUE
VDD
GND
TXD
RXD
CN5 side
CN6 side
PC10
PC12
BOOT0
PB12
PA13
PA14
PC13
PC14
PC15
PH0
PH1
VBAT
PB4
PB9
PC11
PD2
E5V
IOREF
NRST
3V3
VIN
PA0
PA1
PC3
PC2
PC1
PC0
PC9
